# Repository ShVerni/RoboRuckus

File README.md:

# RoboRuckus
RoboRuckus game, currently in progress.

### Installation instructions at https://www.roboruckus.com/documentation

## To do list:
* __Replace discontinued front magnetometer with new part.__
* Modify robot power supply so wheel motors don't run directly off the batteries. Potentially add this boost circuit https://www.adafruit.com/product/1903
* Modify server code to use robot "slide" move (side-to-side movement) and offload the way the robots do that (e.g. turn, move, turn back) to the robots. This allows for robots that can drive sideways to work.
* Design and 3D print new chassis for the robots.
* Create drag n' drop map interface

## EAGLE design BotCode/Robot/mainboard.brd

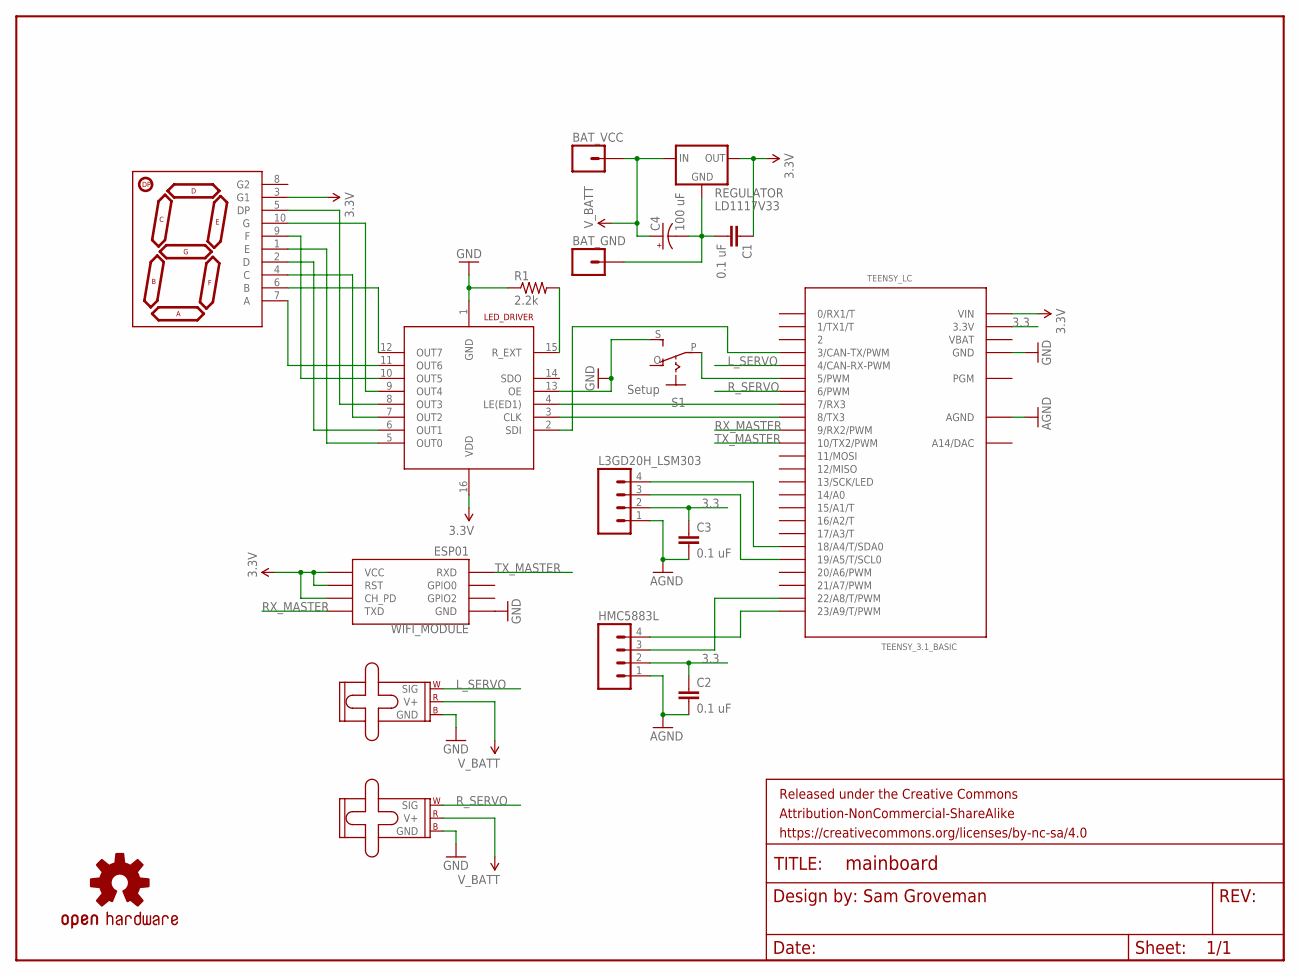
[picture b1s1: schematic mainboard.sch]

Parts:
BAT_GND: M01PTH; 1X01
BAT_VCC: M01PTH; 1X01
C1, C2, C3: 0.1 uF; CAP-PTH-SMALL
C4: 100 uF; CPOL-RADIAL-100UF-25V
FRAME1: FRAME-LETTER; CREATIVE_COMMONS
HMC5883L: M04PTH; 1X04
L3GD20H_LSM303: M04PTH; 1X04
LED_DRIVER: TLC5916/17DIP-16; DIP-16
LOGO1: OSHW-LOGOL; OSHW-LOGO-L
L_SERVO: SMALL_SERVO; 1X03
R1: 2.2k; AXIAL-0.4
REGULATOR: LD1117V33
R_SERVO: SMALL_SERVO; 1X03
S1: Setup; EG1218
TEENSY_LC: TEENSY_3.1_BASIC
U$4: 7-SEGMENT-DISPLAY-1"-RED; 7-SEGMENT-1"PTH
WIFI_MODULE: ESP01

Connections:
3.3: C2.1, C3.1, HMC5883L.2, L3GD20H_LSM303.2, TEENSY_LC.3.3V, TEENSY_LC.3.3V1 (3.3V)
3.3V: C1.1, LED_DRIVER.16 (VDD), REGULATOR.OUT, TEENSY_LC.VIN, U$4.3 (G1), WIFI_MODULE.CH_PD, WIFI_MODULE.RST, WIFI_MODULE.VCC
AGND: C2.2, C3.2, HMC5883L.1, L3GD20H_LSM303.1, TEENSY_LC.AGND
CLK: LED_DRIVER.3 (CLK), TEENSY_LC.8 (8/TX3)
F_SCL: HMC5883L.3, TEENSY_LC.22/A8 (22/A8/T/PWM)
F_SDA: HMC5883L.4, TEENSY_LC.23/A9 (23/A9/T/PWM)
GND: BAT_GND.1, C1.2, C4.2 (-), LED_DRIVER.1 (GND), LED_DRIVER.13 (OE), L_SERVO.3 (GND), R1.P$1 (1), REGULATOR.GND, R_SERVO.3 (GND), S1.S, TEENSY_LC.GND, TEENSY_LC.GND1 (GND), WIFI_MODULE.GND
LE: LED_DRIVER.4 (LE(ED1)), TEENSY_LC.7 (7/RX3)
LED_1: LED_DRIVER.5 (OUT0), U$4.1 (E)
LED_2: LED_DRIVER.6 (OUT1), U$4.2 (D)
LED_4: LED_DRIVER.7 (OUT2), U$4.4 (C)
LED_5: LED_DRIVER.8 (OUT3), U$4.5 (DP)
LED_6: LED_DRIVER.12 (OUT7), U$4.6 (B)
LED_7: LED_DRIVER.11 (OUT6), U$4.7 (A)
LED_9: LED_DRIVER.10 (OUT5), U$4.9 (F)
LED_10: LED_DRIVER.9 (OUT4), U$4.10 (G)
L_SERVO: L_SERVO.1 (SIG), TEENSY_LC.4 (4/CAN-RX-PWM)
RX_MASTER: TEENSY_LC.9 (9/RX2/PWM), WIFI_MODULE.TX (TXD)
R_EXT: LED_DRIVER.15 (R_EXT), R1.P$2 (2)
R_SCL: L3GD20H_LSM303.3, TEENSY_LC.19/A5 (19/A5/T/SCL0)
R_SDA: L3GD20H_LSM303.4, TEENSY_LC.18/A4 (18/A4/T/SDA0)
R_SERVO: R_SERVO.1 (SIG), TEENSY_LC.6 (6/PWM)
SDI: LED_DRIVER.2 (SDI), TEENSY_LC.3 (3/CAN-TX/PWM)
SETUP: S1.P, TEENSY_LC.5 (5/PWM)
TX_MASTER: TEENSY_LC.10 (10/TX2/PWM), WIFI_MODULE.RX (RXD)
VBAT: TEENSY_LC.VBAT
V_BATT: BAT_VCC.1, C4.1 (+), L_SERVO.2 (V+), REGULATOR.IN, R_SERVO.2 (V+)

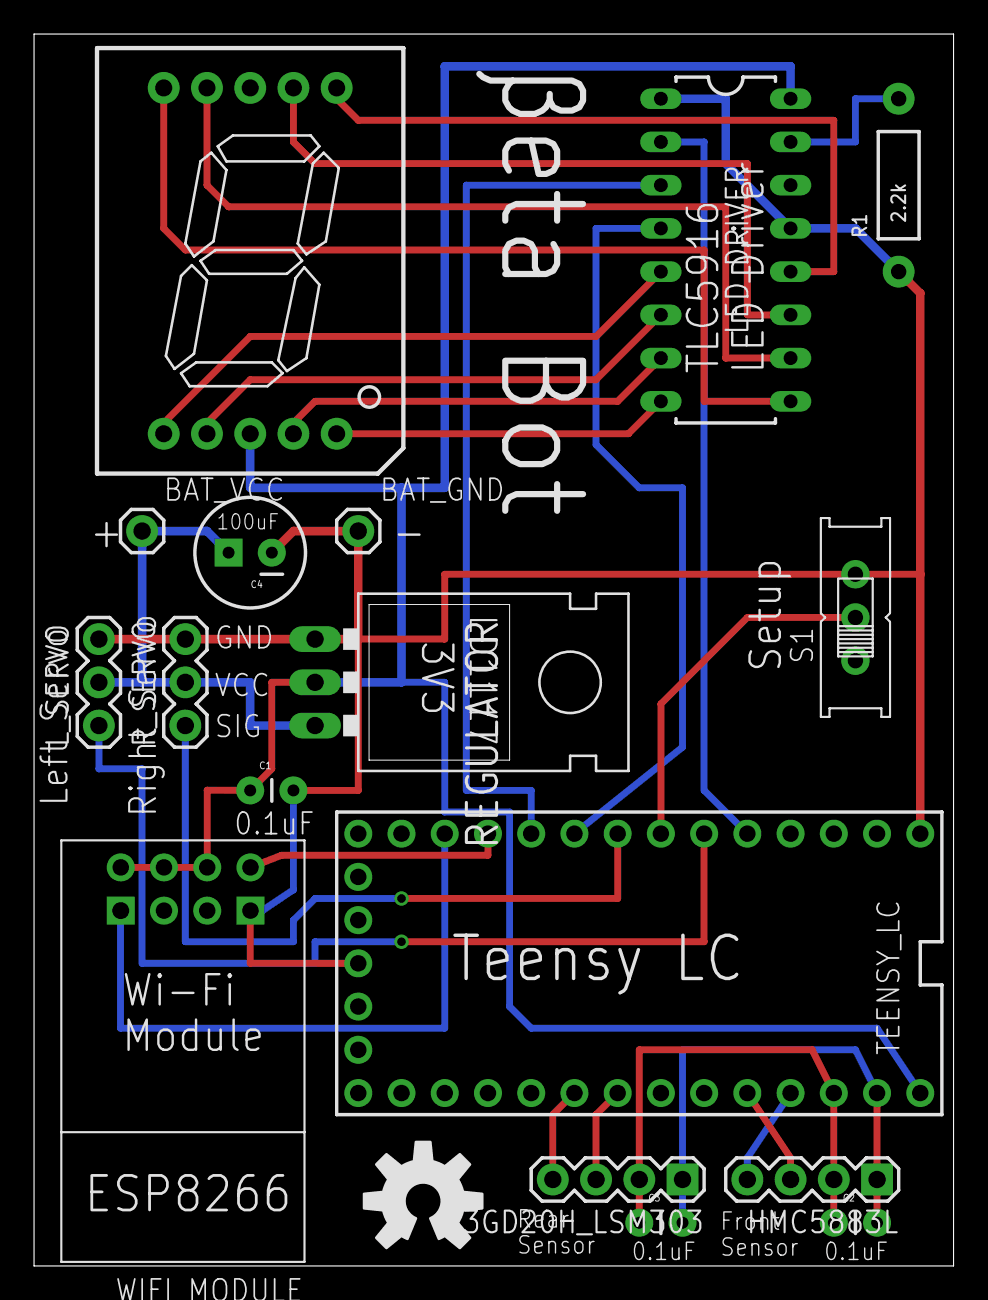
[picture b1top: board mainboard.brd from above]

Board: 2 copper layers, 54.0 x 72.4 mm, 19 parts (0 on the bottom side), 26 nets.

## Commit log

2015-10-28 Fixed spelling error of "Environment"
2015-10-28 Removed command "web"
2015-10-28 Fixed typo in comment
2015-11-03 Made movement card loader more effcient
2015-11-14 Enabled shutdown toggle, fixed comments
2015-11-15 Numerous changes, mainly involving the implementation of game boards and the following board effects: Board lasers, turntables, pits, wrenches, and walls.
2015-11-16 Fixed a bug in the lasers and in the bot code.
2015-11-16 Fixed laser damage calculations to allow for simultaneous damage.
2015-11-17 Added initial support for conveyor belts.
2015-11-18 User interface changes.
2015-11-18 Fixed bug in lasers, made use of lock statements consistent. The somewhat overcautious use of lock statements may be revised.
2015-11-18 Updated howler.js
2015-11-18 User interface fixes.
2015-11-19 Fixed UI bug.
2015-11-22 Superfluous file removed
2015-11-22 Added support for flags and win conditions.
2015-11-22 Fix merging issues
2015-11-22 Added winning music,
2015-11-22 Fixed typo from previous commit.
2015-11-24 Added support for robot names
2015-11-24 Fixed bug in victory music
2015-11-24 Minor UI improvement.
2015-11-25 Added player lives.
2015-11-25 Added more game reset options.
2015-11-26 Fixed bug in robot re-entry code.
2015-11-26 Updated robot BOM.
2015-11-27 Updated robot movement code.
2015-11-27 Fixed bug in conveyor movement code.
2015-11-27 Fixed bug left from testing
2015-11-27 Fixed bug in reset code.
2015-12-05 Added support for "deathmatch" mode.
2015-12-08 Fixed bugs in player shutdown and move submission code.
2015-12-08 Fixed flag UI bug,
2015-12-08 Fixed bug left from testing.
2015-12-09 UI Improvements.
2015-12-09 Added flag touch sound effects.
2015-12-13 Deleted superfluous file
2015-12-17 UI improvements
2015-12-29 General bug fixes.
2015-12-29 Added board assets
2015-12-31 Updated to ASP.Net RC1
2015-12-31 UI improvements and general fixes.
2015-12-31 UI Fixes
2015-12-31 Fixed bug in bot code.
2016-01-02 Added missing board elements asset files
2016-01-16 Added support for the player timer.
2016-01-16 Updated timer code, minor fixes.
2016-01-16 Fixed typo
2016-01-16 Minor fixes
2016-01-18 Added timer sounds.
2016-01-18 Made manual URL navigation safer.
2016-01-20 Timer bug fixes and minor updates.
2016-01-22 Added executing register indicator.
2016-01-22 Fixed Readme.md
2016-01-28 Some cleanup from beta8 to RC1 transition; more is needed
2016-02-02 Rebase
2016-02-02 Fixed bug in card dealing.
2016-02-02 Fixed bug in flag touch sound.
2016-03-20 Updates to robot code, fixes for game sounds and new sounds, UI fixes.
2016-03-28 Updated bot movement code to be more reliable.
2016-03-29 Added new board.
2016-04-02 Updated UI to incude player management
2016-04-02 Fixed bug in player management code.
2016-04-16 Updated shutdown, wrench, and flag code to be more rules compliant.
2016-04-25 UI improvements and bug fixes for player management.
2016-04-25 Added assets for flag decals.
2016-04-28 Updates timer toggle UI.
2016-04-28 Update Howler.js and jQuery libraries.
2016-05-01 Typo fixes, minor changes.
2016-05-10 Fixed edge case bug in shutdown code, improved player UI, added robot victory dance.
2016-05-11 Updated bot code movement.
2016-05-11 Fixed commetns.
2016-06-07 Updated UI and improved failsafe timeouts for unresponsive bots.
2016-06-07 Fixed bugs in bot movement code.
2016-06-09 Fixed bug for robots that are destroyed mid-register.
2016-06-09 Updated UI.
2016-06-23 Updated adding robot code to account for DHCP issues (needs testing).
2016-07-26 Fixed copyright and license.
2016-07-30 Initial update from ASP.Net 5 RC1 to .Net Core 1.0.0
2016-07-31 Added switch for playing/testing without physical robots.
2016-08-06 Applied fixes to get ASP.Net Core to work on Raspberry Pi.
2016-08-06 Clean up.
2016-08-06 Further clean up.
2016-10-29 Bug fix from update
2016-10-30 Added link to documentation.
2017-02-07 Migrated to ASP.Net Core 1.1.0, updated jQuery plugins.
2017-02-08 Updated to jquery 2.2.4, fixed font size bug.
2017-03-26 Updated for ASP.Net 1.1.1 and added "botless" launch switch.
2017-04-05 Fixed Readme.
2017-05-16 Updated to .Net 4.7 and added start button functionality.
2017-06-22 Added player status checker, UI improvements, updated jQuery plugins.
2017-06-22 Updated readme with to do list.
2017-09-13 Updated to ASP.Net Core 2.0, added edgecontrol, fixed bug that marked bots dead to early.
2018-01-20 Fixed bugs with string variables.
2018-02-18 Added initial support for robot tuning.
2018-02-18 Added source code for initial bot tuning apps.
2018-02-18 Fixed assembly info and updated dependancies.
2018-05-19 Fixed typos.
2018-05-19 Added image,
2018-05-24 Fixed IIS settings bug
2018-06-02 Upgraded to ASP.Net Core 2.1
2018-06-06 Fixed gerbers.
2018-06-26 Updated to .Net Core SDK 2.1.301
2018-06-26 Updated Howler library.
2018-06-26 Added check for botless mode in bot tuning.
2018-07-07 Replaced discontinued 9-DOF board.
2018-07-08 Code cleanup.
2018-07-13 Fixed referenes to correct 9-DOF sensor.
2018-07-13 Fixed rear magnetometer axes.
2018-08-26 Added baord maker. Moved to NPM for JavaScript library managments. General fixes.
2018-08-27 Removed leftover debug code.
2018-09-09 Added node_modules for convenience. Fixed bug.
2018-09-09 Upted Pi Ready files.
2018-09-09 User interface changes for boardMaker.
    -added two stage setup
    -added fading effect
    -swapped board and element position
2018-09-09 Fix board selection glitch.
2018-09-09 More fixes
2018-09-10 Fixed right click on boardMaker
2018-10-07 Bug fix.
2018-10-07 Removed unnecessary node modules.
2018-10-07 Fixed ignore file.
2021-08-29 Upgrade to .NET 5 and initial changes for modular bot communication methods.
2021-08-29 Added missing JSON package.
2021-08-29 Cleanup
2021-08-29 Added Bluetooth support place holders.
2021-09-04 Replaced obsolete crypto provider.
2021-10-08 Added option to show entire register each round.
2021-10-08 Updates, and added systemd service files.
2021-10-15 Updating liscense.
2021-10-15 Updated License.
2021-10-15 Rename LISCENSE.md to LISCENSE.md.old
2021-10-20 Added extensible bot tuning system.
2021-10-28 Added \n terminator to all bot messages
2021-11-14 Updated to .Net 6
2022-01-08 Comment typo fixes
2022-02-26 Add files for vscode Remote-Containers dev
2022-02-27 Migrated board image maker to SkiaSharp
2022-04-17 Added tuning slider buttons
2022-05-20 Compacted output to single file
2022-06-09 Initial lateral robot movement support and UI enhancements.
2022-06-09 Updated ARM Publish
2022-06-09 Clean up
2022-08-27 Added logging
    Added switch to enable logging of the game play
2022-08-27 Logging fix
    Removed unnecessary logging info
2022-09-05 Fixed bugs in game logger
    Fixed bugs in new game logging code that would cause hangs and ignore command line arguments.
2022-09-05 Updated Pi ready code
2022-09-05 Added basic update scrtipt
2023-01-28 Heal on every register
    Changed rules to heal every register. Could make this a toggle in the future

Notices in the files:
parts and their libraries:
SparkFun-Connectors: Licensing: Creative Commons ShareAlike 4.0 International - https://creativecommons.org/licenses/by-sa/4.0
SparkFun-Aesthetics: https://creativecommons.org/licenses/by-nc-sa/4.0
SparkFun-Aesthetics: Released under the Creative Commons
